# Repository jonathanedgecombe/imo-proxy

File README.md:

A hardware USB/HID proxy designed for the IntelliMouse Optical 1.1A. Overclocks to 1000Hz polling rate and adds switch debouncing.

Other mice could be supported by modifying the report descriptors & report parsing, or implementing a complete report descriptor parser.

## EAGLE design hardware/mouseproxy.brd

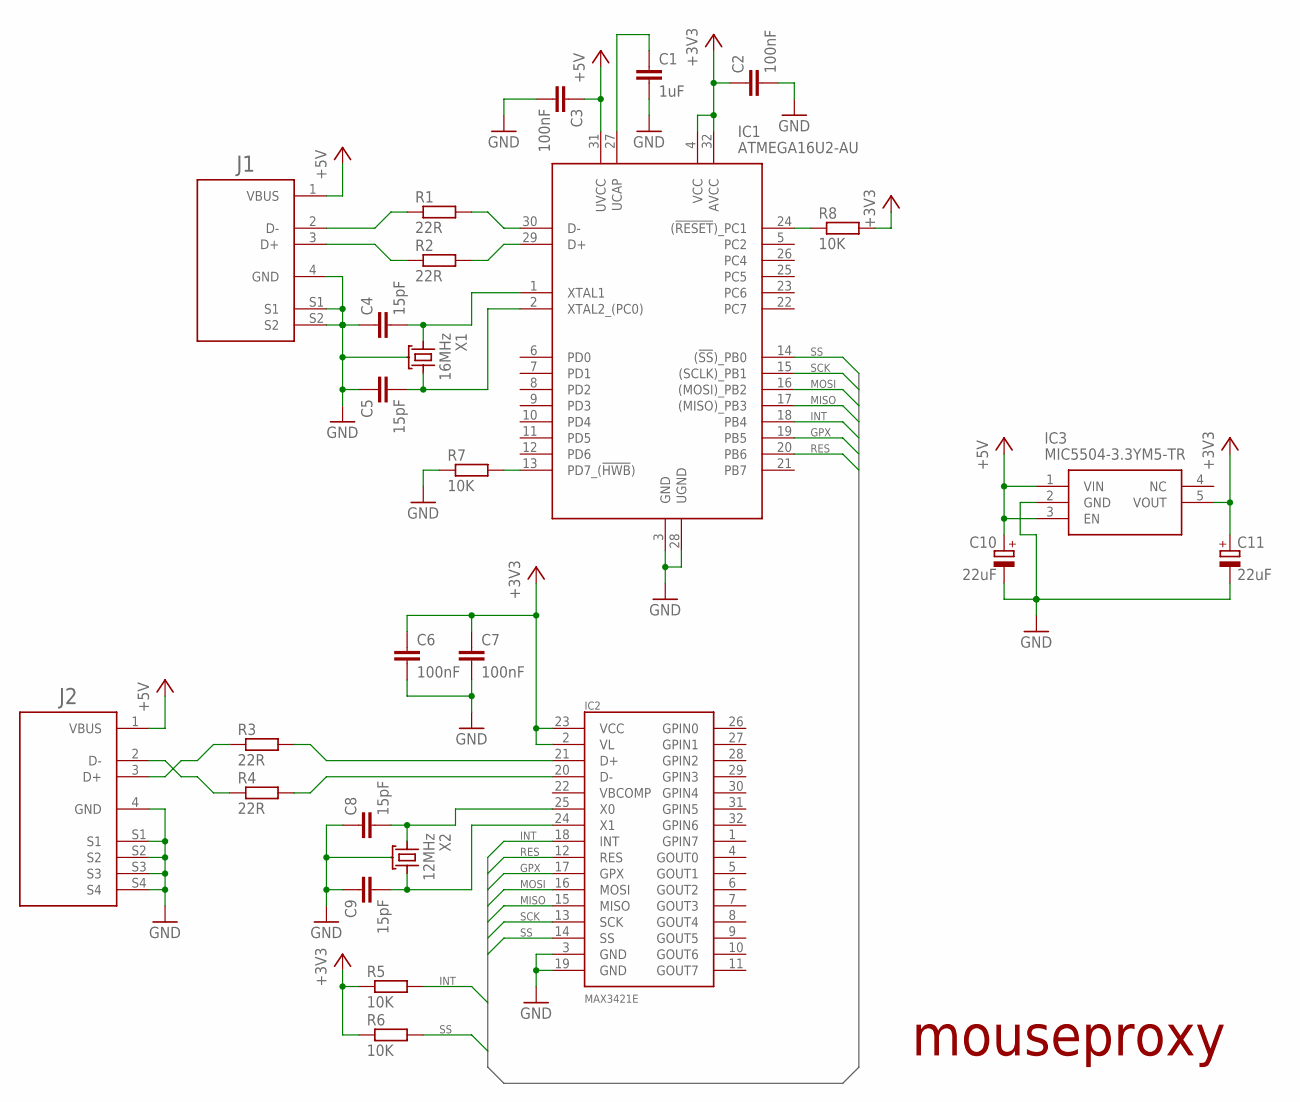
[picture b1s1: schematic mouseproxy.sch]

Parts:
C1: 1uF; 0603
C2, C3, C6, C7: 100nF; 0603
C4, C5, C8, C9: 15pF; 0603
C10, C11: 22uF; 1206POL
IC1: ATMEGA16U2-AU; QFP80P900X900X120-32N
IC2: MAX3421E; TQFP32-5MM
IC3: MIC5504-3.3YM5-TR; SOT95P280X130-5N
J1: 48037-0001
J2: 48258-0001
R1, R2, R3, R4: 22R; 0603
R5, R6, R7, R8: 10K; 0603
X1: 16MHz; 3.2X2.5_4
X2: 12MHz; 3.2X2.5_4

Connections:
+3V3: C2.1, C6.1, C7.1, C11.1 (+), IC1.4 (VCC), IC1.32 (AVCC), IC2.2 (VL), IC2.23 (VCC), IC3.5 (VOUT), R5.1, R6.1, R8.2
+5V: C3.1, C10.1 (+), IC1.31 (UVCC), IC3.1 (VIN), IC3.3 (EN), J1.1 (VBUS), J2.1 (VBUS)
D_F_N: IC1.30 (D-), R1.2
D_F_P: IC1.29 (D+), R2.2
D_N: J1.2 (D-), R1.1
D_P: J1.3 (D+), R2.1
GND: C1.2, C2.2, C3.2, C4.1, C5.1, C6.2, C7.2, C8.1, C9.1, C10.2 (-), C11.2 (-), IC1.3 (GND), IC1.28 (UGND), IC2.3 (GND), IC2.19 (GND), IC3.2 (GND), J1.4 (GND), J1.S1, J1.S2, J2.4 (GND), J2.S1, J2.S2, J2.S3, J2.S4, R7.1, X1.P$2 (GND), X1.P$4 (GND), X2.P$2 (GND), X2.P$4 (GND)
GPX: IC1.19 (PB5), IC2.17 (GPX)
HOST_D_N: J2.2 (D-), R4.1
HOST_D_P: J2.3 (D+), R3.1
HOST_F_D_N: IC2.20 (D-), R4.2
HOST_F_D_P: IC2.21 (D+), R3.2
INT: IC1.18 (PB4), IC2.18 (INT), R5.2
MISO: IC1.17 ((MISO)_PB3), IC2.15 (MISO)
MOSI: IC1.16 ((MOSI)_PB2), IC2.16 (MOSI)
unnamed: C5.2, IC1.2 (XTAL2_(PC0)), X1.P$3 (XT2)
unnamed: C4.2, IC1.1 (XTAL1), X1.P$1 (XT1)
unnamed: C1.1, IC1.27 (UCAP)
unnamed: C9.2, IC2.24 (X1), X2.P$3 (XT2)
unnamed: C8.2, IC2.25 (X0), X2.P$1 (XT1)
unnamed: IC1.13 (PD7_(!HWB!)), R7.2
unnamed: IC1.24 ((!RESET!)_PC1), R8.1
RES: IC1.20 (PB6), IC2.12 (RES)
SCK: IC1.15 ((SCLK)_PB1), IC2.13 (SCK)
SS: IC1.14 ((!SS!)_PB0), IC2.14 (SS), R6.2

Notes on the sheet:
mouseproxy

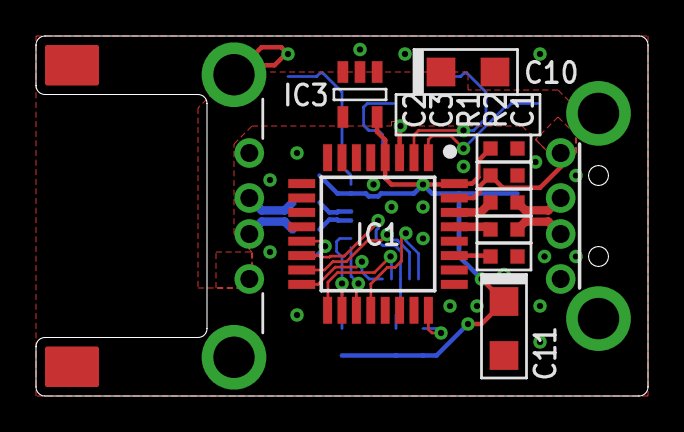
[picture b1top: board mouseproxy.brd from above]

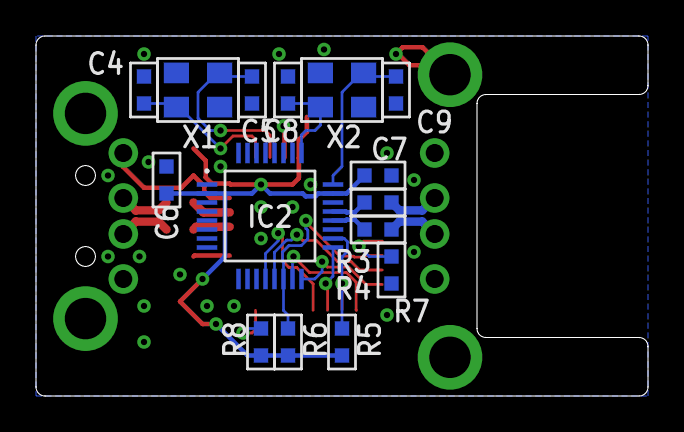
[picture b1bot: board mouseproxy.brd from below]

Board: 2 copper layers, 34.0 x 20.0 mm, 26 parts (15 on the bottom side), 25 nets.

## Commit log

2020-07-24 Initial commit.
2021-02-24 Add PCB
2021-02-24 Add board photos and renders
2021-02-24 Add .gitignore
2021-02-24 Add readme
2021-02-24 Formatting
2021-02-24 Reword readme
2021-02-24 Add license
2021-02-24 Update README.md
    Typo
